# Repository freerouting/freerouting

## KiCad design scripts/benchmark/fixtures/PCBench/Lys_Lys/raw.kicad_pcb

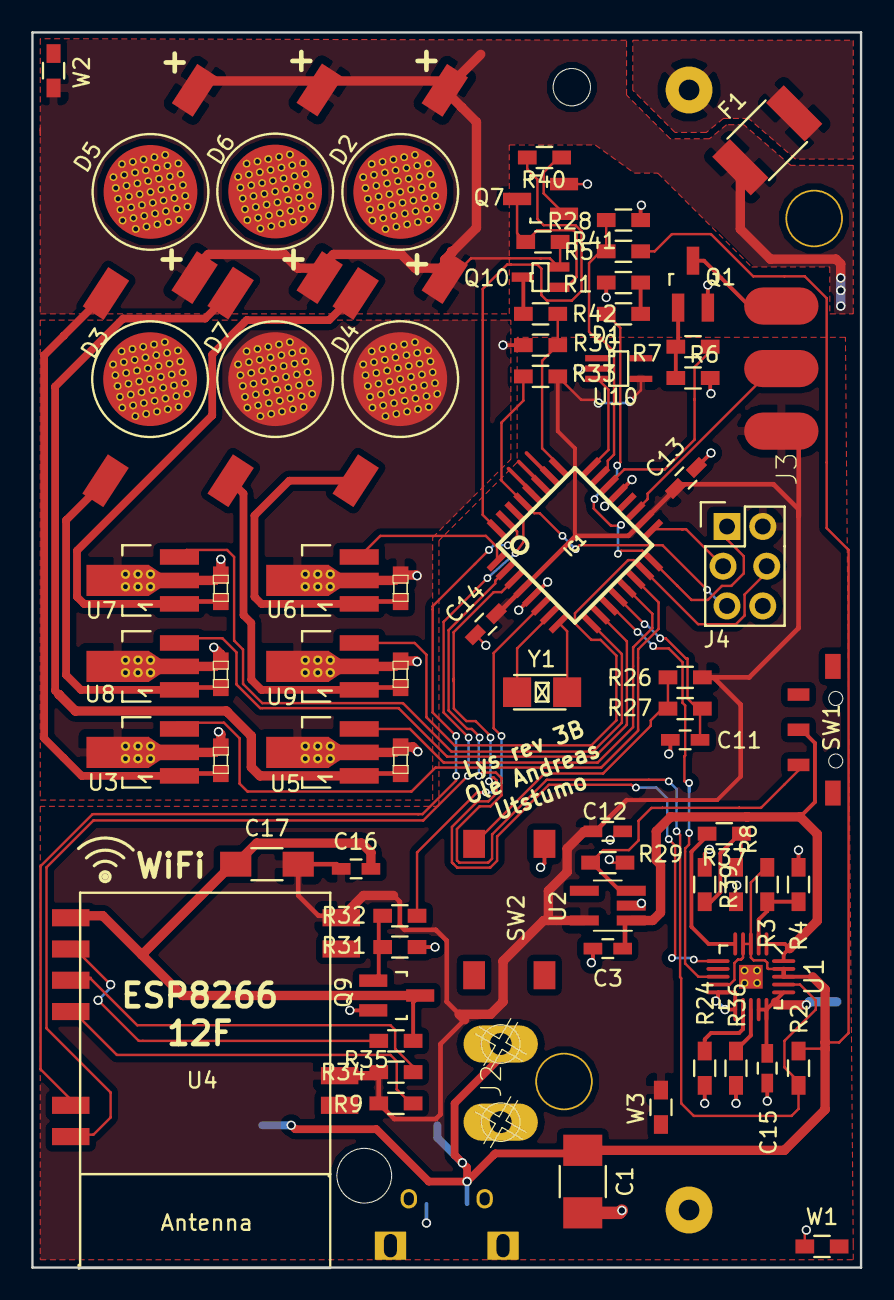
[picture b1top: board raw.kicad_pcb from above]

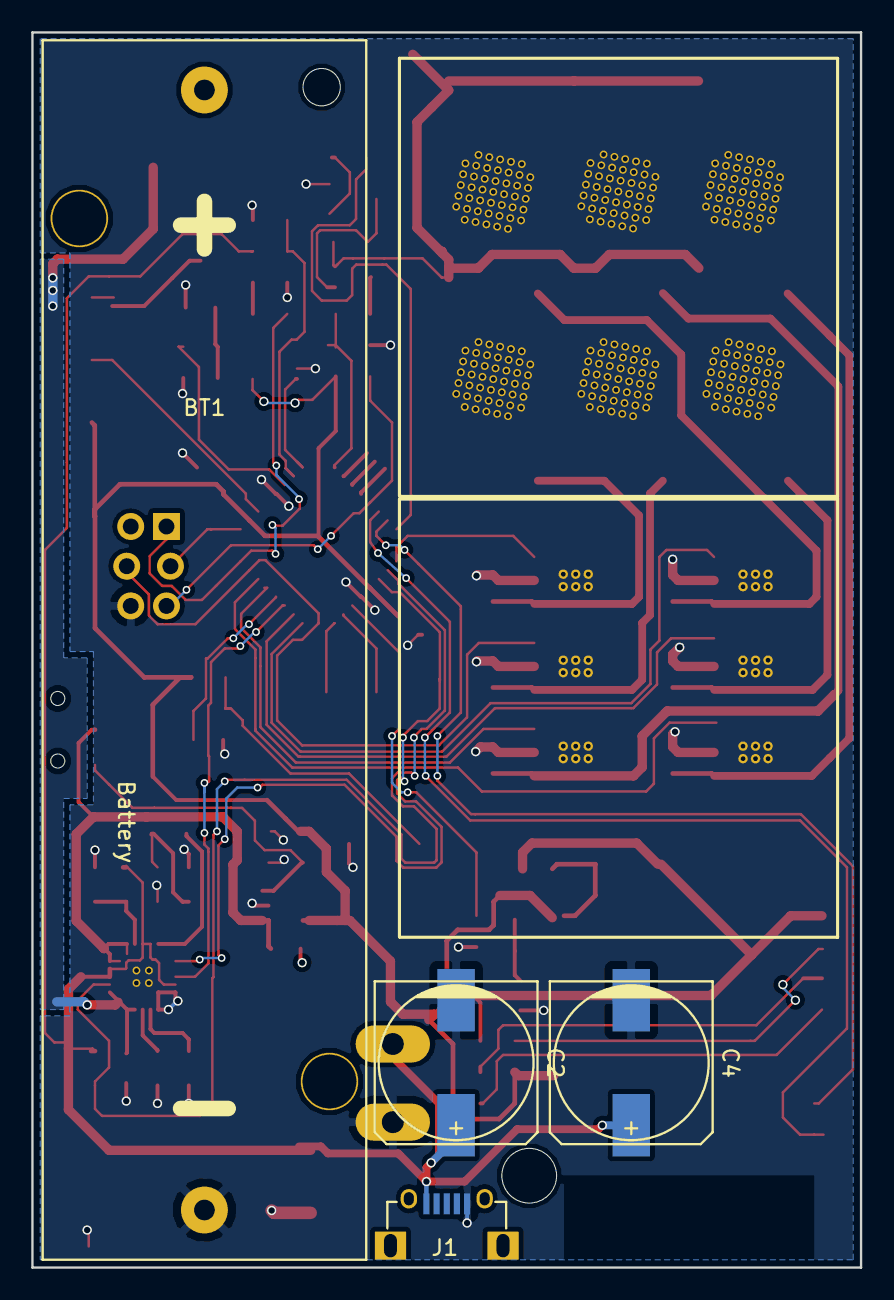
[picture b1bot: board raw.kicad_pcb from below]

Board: 2 copper layers, 53.0 x 79.0 mm, 77 parts (4 on the bottom side), 54 nets.

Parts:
BT1: Battery; Keystone_1043_1860_holder
C1: 0.1u; C_1210_HandSoldering
C2, C4: CAPACITOR_POL-CASE_A; c_elec_10x10
C3, C15: 0.1u; C_0603_HandSoldering
C5, C6, C7, C8, C9, C10: C; dp_devices-C603
C11, C13, C14, C16: 0.1uF; C_0603_HandSoldering
C12: 1uF; C_0603_HandSoldering
C17: 10uF; C_1206_HandSoldering
D1: LED; R_0603_HandSoldering
D2, D3, D4, D5, D6, D7: LED; 1W_LED_bead_1
F1: FUSE; R_1812
IC1: ATMEGA168PB-AU; TQFP32-7x7
J1: USBJACK_micro; Multicomp_MC001009_handsolder
J2: CON_TERMINAL_BLOCK_02-5MM; Wire_terminal_x2
J3: CON_HEADER_1X03-PTH; Wire_Solder_Pads_x3_SMD
J4: CON_HEADER_2X03-PTH; SPI_Header_SnapIn
Q1, Q9: TSM2306; SOT-23_Handsoldering
Q7: PBSS4120T; SOT-23_Handsoldering
Q10: NX3008PBKW; SOT-323_handsoldering
R1, R5, R26, R28, R30, R33, R40, R41, R42: 10k; R_0603_HandSoldering
R2, R3, R4: 27k; R_0603_HandSoldering
R6, R31: 100k; R_0603_HandSoldering
R7, R27, R32: 200; R_0603_HandSoldering
R8, R24, R36, R37, R39: 6.8k; R_0603_HandSoldering
R9, R34, R35: 1k; R_0603_HandSoldering
R29: 1M; R_0603_HandSoldering
SW1: SPST; JS102000SAQN
SW2: SW_PUSH; MC32882
U1: MCP73871; QFN_20
U2: TLV733; SOT-23-5_Handsolder
U3, U5, U6, U7, U8, U9: AMC7135; SOT89-3_ThermalVias_Handsoldering
U4: ESP-12E; ESP8266_12F_handsolder
U10: MCP9700; SC-70-5_handsoldering
W1, W2, W3: TEST_1P; R_0603_HandSoldering
Y1: ABS25-32.768KHZ-6-T; ABS07-32.768KHZ-T

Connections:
+BATT: C15.1, D2.2, D3.2, D4.2, D5.2, D6.2, D7.2, F1.1, Q10.2, R41.1, U1.14, U1.15, U1.16, W2.1
ADC_EXT2: IC1.19, J3.2
ADC_batt: IC1.25, R30.1, R42.2
ADC_solar: IC1.23, R5.1, R28.2
ADC_temp: IC1.24, U10.3
BUTTON: C11.2, IC1.12, R27.1
Battsense_EN: IC1.32, R40.1
Chg_STAT1: IC1.11, U1.8
Chg_en: IC1.2, R2.1, U1.17
Chg_nPG: IC1.3, U1.6
ESP_RX: IC1.31, U4.21
ESP_TX: IC1.30, U4.22
ESP_en: IC1.6, R32.1
EXT_en: IC1.22, R7.1
GND: BT1.2, C1.2, C2.2, C4.2, C5.2, C6.2, C7.2, C8.2, C9.2, C10.2, C11.1, C12.2, C13.1, C14.1, C15.2, D2.0, D3.0, D4.0, D5.0, D6.0, D7.0, IC1.5, IC1.21, J1.5, J2.1, J4.6, Q1.2, Q7.2, Q9.2, R1.2, R4.1, R6.1, R8.1, R24.1, R28.1, R29.1, R30.2, R31.1, R36.1, R39.1, SW2.2, U1.0, U1.10, U1.11, U1.EP, U2.2, U3.0, U3.2, U5.0, U5.2, U6.0, U6.2, U7.0, U7.2, U8.0, U8.2, U9.0, U9.2, U10.2, W1.1
MISO: D1.2, IC1.16, J4.1
MOSI: IC1.15, J4.4, U9.3
unnamed: BT1.1, F1.2
unnamed: C5.1, D5.1, U3.1
unnamed: C6.1, D6.1, U5.1
unnamed: C7.1, D4.1, U6.1
unnamed: C8.1, D2.1, U7.1
unnamed: C9.1, D3.1, U8.1
unnamed: C10.1, D7.1, U9.1
unnamed: C16.1, C17.1, Q9.3, R35.1, U4.15
unnamed: D1.1, R1.1
unnamed: J3.3, Q1.3
unnamed: Q1.1, R6.2, R7.2
unnamed: Q7.1, R40.2
unnamed: Q9.1, R31.2, R32.2
unnamed: Q7.3, Q10.1, R41.2
unnamed: Q10.3, R42.1
unnamed: R3.1, R4.2, U1.2
unnamed: R9.2, U4.18
unnamed: R24.2, U1.12
unnamed: R26.1, R27.2, SW2.1
unnamed: R29.2, SW1.1, U2.3
unnamed: R34.2, U4.17
unnamed: R35.2, U4.16
unnamed: R36.2, U1.13
unnamed: R37.1, U1.5
unnamed: R8.2, R37.2, R39.2
PWM_LED1: IC1.9, U7.3
PWM_LED2: IC1.13, U5.3
PWM_LED3: IC1.14, U3.3
PWM_LED4: IC1.1, U6.3
PWM_LED5: IC1.10, U8.3
SCK: IC1.17, J4.3
VCC: C12.1, C13.2, C14.2, C16.2, C17.2, IC1.4, IC1.18, J3.1, J4.2, R9.1, R26.2, R33.1, R34.1, U2.5, U4.3, U4.8, U10.4, W3.1
VDD: SW1.2, U1.1, U1.20, U2.1
VPP: C1.1, C2.1, C4.1, J1.1, J2.2, R2.2, R3.2, R5.2, U1.3, U1.4, U1.9, U1.18, U1.19
XTAL1: IC1.7, Y1.1
XTAL2: IC1.8, Y1.2
nRESET: IC1.29, J4.5, R33.2

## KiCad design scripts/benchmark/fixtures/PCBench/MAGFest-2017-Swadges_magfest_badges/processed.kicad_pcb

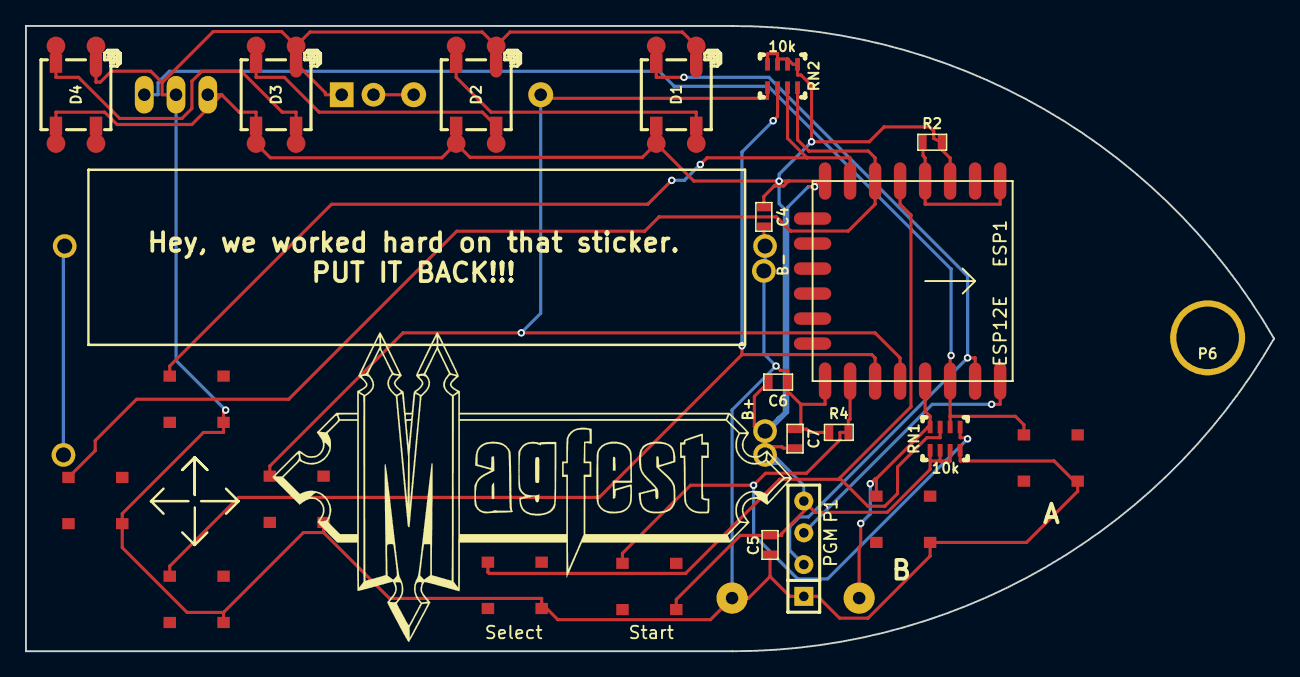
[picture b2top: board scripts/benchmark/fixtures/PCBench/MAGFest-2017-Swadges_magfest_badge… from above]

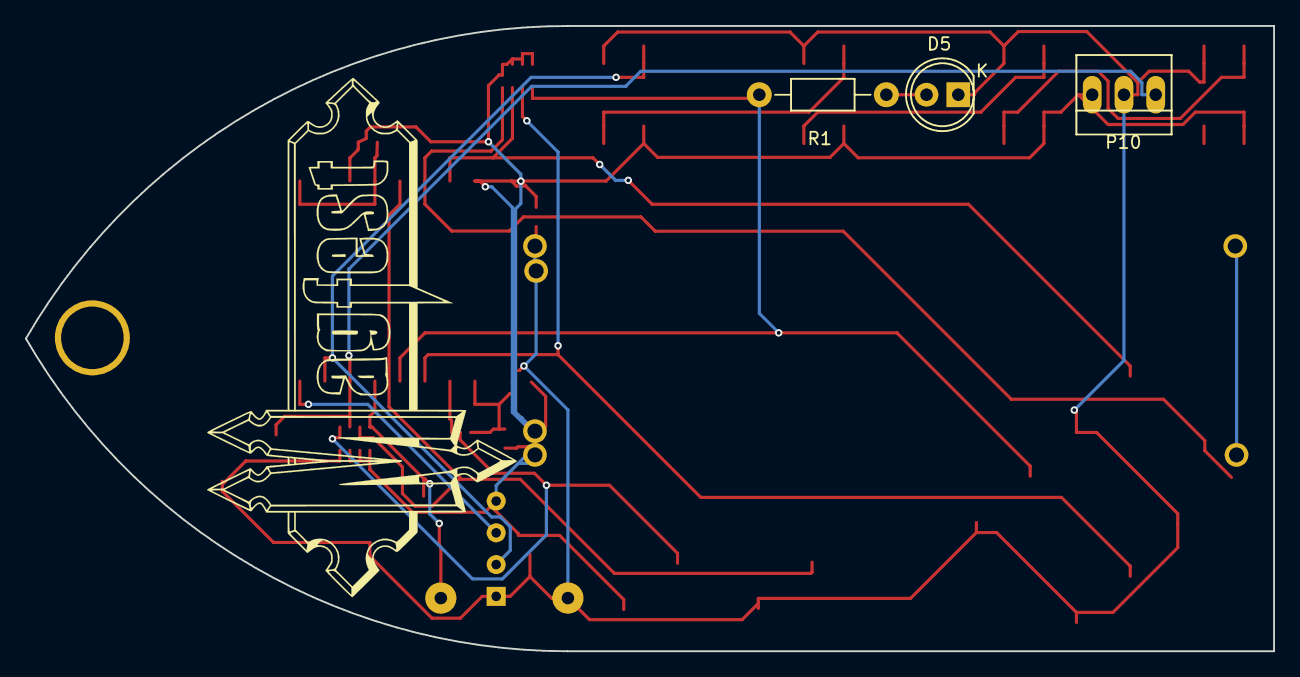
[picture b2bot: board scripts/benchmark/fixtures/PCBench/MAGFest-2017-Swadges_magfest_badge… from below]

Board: 2 copper layers, 99.8 x 50.0 mm, 34 parts (5 on the bottom side), 18 nets.

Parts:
C4, C5: 10u; SM0603
C6, C7: .1u; SM0603
D1, D2, D3, D4: WS2812B; WS2812BQ
D5: LED; LED-5MM
ESP1: ESP12E
G1: LOGO; outline
P1: PGM; RECT_4x1
P3, P5: B+; SMTPIN
P4, P7: B-; SMTPIN
P6: HOLE_LANYARD; SMTPIN
P8, P9: 1.5; SMTPIN
P10: CONN_01X03; PINHEAD1-3
R1: R; Resistor_Horizontal_RM10mm
R2, R4: 12k; SM0603
RN1, RN2: 10k; NETWORK1206
SP1: SPEAKER; BUZZER
SW1, SW2, SW3, SW4, SW5, SW6, SW7, SW8: TACTILE

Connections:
+3V3: C4.1, C5.1, C6.1, C7.1, D1.1, D2.1, D3.1, D4.1, ESP1.3, ESP1.8, P1.4, P3.1, P5.1, P10.3, R2.2, RN1.5, RN1.6, RN1.7, RN2.5, RN2.6, RN2.7, RN2.8, SW5.4
GND: C4.2, C5.2, C6.2, C7.2, D1.3, D2.3, D3.3, D4.3, D5.1, ESP1.15, P1.1, P4.1, P7.1, P10.2, R4.2, RN1.8, SP1.2, SW1.4, SW2.4, SW3.4, SW4.4, SW6.4, SW7.4, SW8.4
GP0: ESP1.18, R1.2, RN2.1, SW2.1
GP2: ESP1.17, RN2.2, SW4.1
GP4: ESP1.19, RN1.4, SP1.1, SW3.1
GP5: ESP1.20, P10.1, RN1.2, SW1.1
GP12: ESP1.6, RN2.4, SW8.1
GP13: ESP1.7, RN2.3, SW6.1
GP14: ESP1.5, RN1.3, SW7.1
GP15: ESP1.16, R4.1, RN1.1, SW5.1
unnamed: D1.2, D2.4
unnamed: D2.2, D3.4
unnamed: D3.2, D4.4
unnamed: D5.2, R1.1
RESET: ESP1.1, ESP1.4, R2.1
URX: D1.4, ESP1.21, P1.2
UTX: ESP1.22, P1.3
V15: P8.1, P9.1

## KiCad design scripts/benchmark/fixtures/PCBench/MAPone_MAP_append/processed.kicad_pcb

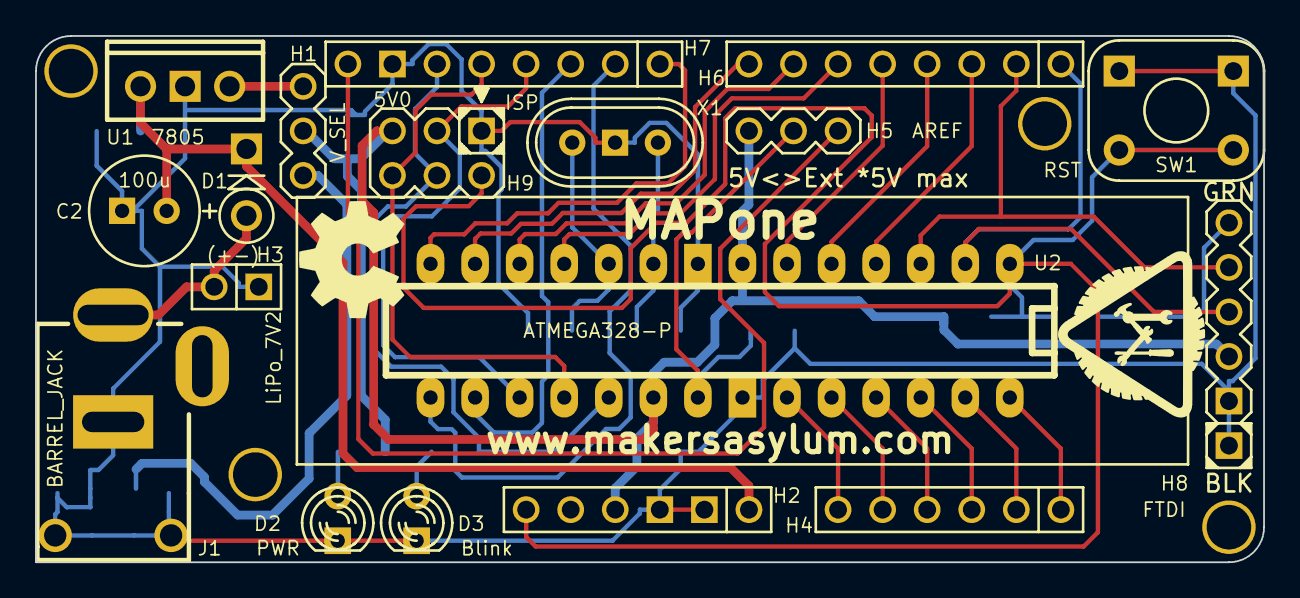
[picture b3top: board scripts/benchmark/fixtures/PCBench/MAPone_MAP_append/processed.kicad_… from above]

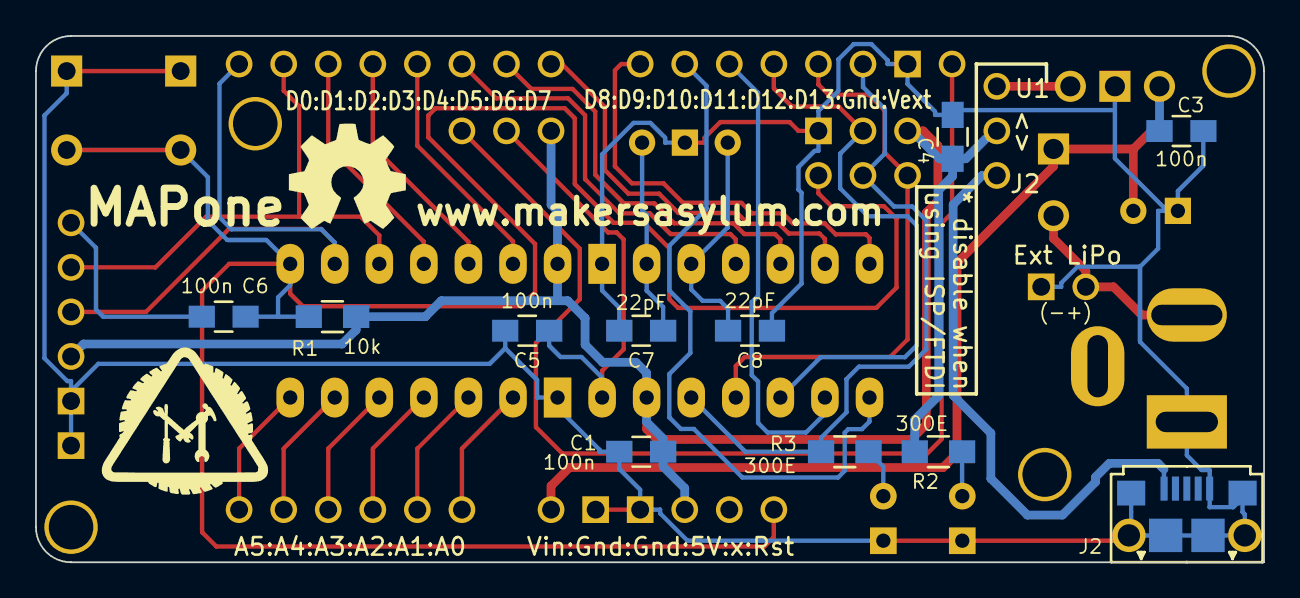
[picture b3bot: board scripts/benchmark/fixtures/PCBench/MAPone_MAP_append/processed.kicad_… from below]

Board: 2 copper layers, 70.0 x 30.0 mm, 37 parts (13 on the bottom side), 34 nets.

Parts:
C1, C3, C4, C5, C6: 100n; C_0805_HandSoldering
C2: 100u; Elko_vert_11.2x6.3mm_RM2.5
C7, C8: 22pF; C_0805_HandSoldering
D1: 1N4007; Diode_DO-41_SOD81_Vertical_KathodeUp
D2: PWR; LED-3MM
D3: Blink; LED-3MM
H1: V_SEL; Header_3
H2: Power; Socket_Strip_Straight_1x06
H3: LiPo_7V2; Pin_Header_Straight_1x02
H4: ANALOG; Socket_Strip_Straight_1x06
H5: AREF; Header_A_REF
H6: IO_L; Socket_Strip_Straight_1x08
H7: IO_H; Socket_Strip_Straight_1x08
H8: FTDI; Header_FTDI
H9: ISP; Header_ICSP
J1: BARREL_JACK; JACK_ALIM
J2: USB-Micro; USB_B_Micro
P1, P2, P3, P4: CONN_1; vite_3mm
R1: 10k; R_0805_HandSoldering
R2, R3: 300E; R_0805_HandSoldering
SW1: RST; SW-PB
U1: 7805; LM78XXV
U2: ATMEGA328-P; DIP-28__300_ELL_ZIF
X1: 16MHz; Crystal_HC49-U_Vertical_3Pin
Z1, Z2: CONN_1; MA_Logo2
Z6, Z7: CONN_1; OSHW_6mm

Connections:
/5V: C1.1, C4.1, H1.2, H2.4, H5.1, H8.3, H9.2, R1.1, R2.2, U2.7, U2.20
/AD0: H4.6, U2.23
/AD1: H4.5, U2.24
/AD2: H4.4, U2.25
/AD3: H4.3, U2.26
/AD4_SDA: H4.2, U2.27
/AD5_SCL: H4.1, U2.28
/AREF: C5.1, H5.2, U2.21
/MISO: H7.5, H9.1, U2.18
/MOSI_P: H7.4, H9.4, U2.17
/PB0: H7.1, U2.14
/PB1_P: H7.2, U2.15
/PD2: H6.3, U2.4
/PD3_P: H6.4, U2.5
/PD4: H6.5, U2.6
/PD5_P: H6.6, U2.11
/PD6_P: H6.7, U2.12
/PD7: H6.8, U2.13
/RST: C6.1, H2.6, H9.5, R1.2, SW1.2, U2.1
/RXD: H6.1, H8.4, U2.2
/SCK: H7.6, H9.3, R3.1, U2.19
/SS_P: H7.3, U2.16
/TXD: H6.2, H8.5, U2.3
/V_IN: C2.1, C3.2, D1.2, H2.1, U1.VI
/V_REG: H1.1, U1.VO
/V_USB: H1.3, J2.1
/Vext: H5.3, H7.8
GND: C1.2, C2.2, C3.1, C4.2, C5.2, C7.2, C8.2, D2.2, D3.2, H2.2, H2.3, H3.1, H7.7, H8.1, H8.2, H9.6, J1.2, J2.5, J2.T1, J2.T2, J2.T3, J2.T4, J2.T5, J2.T6, SW1.1, U1.GND, U2.8, U2.22, X1.3
unnamed: C6.2, H8.6
unnamed: C7.1, U2.9, X1.1
unnamed: C8.1, U2.10, X1.2
unnamed: D1.1, H3.2, J1.1
unnamed: D2.1, R2.1
unnamed: D3.1, R3.2
